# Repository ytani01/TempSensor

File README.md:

# 環境センサー類(温度、湿度など)

* [BME280](BME280/)
* [SHT-31](SHT-31/)

## beebottle python library

https://github.com/beebotte/bbt_python

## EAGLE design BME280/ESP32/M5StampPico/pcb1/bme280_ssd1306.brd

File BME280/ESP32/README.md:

# BME280(I2C) and ESP32

## !! IMPORTANT !!

FORCEDモードにしないと、温度がかなり高めにでる!

```c++
:
#include <Adafruit_BME280.h>

const uint8_t I2CADDR_BME280 = 0x76;

Adafruit_BME280 bme;

void setup() {

  bme.begin(I2CADDR_BME280);
  bme.setSampling(Adafruit_BME280::MODE_FORCED);  // !! IMPORTANT !!

}

void loop() {

  bme.takeForcedMeasurement();  // !! IMPORTANT !!

  float temp = bme.readTemperature();
  float humidity = bme.readHumidity();
  
}
```

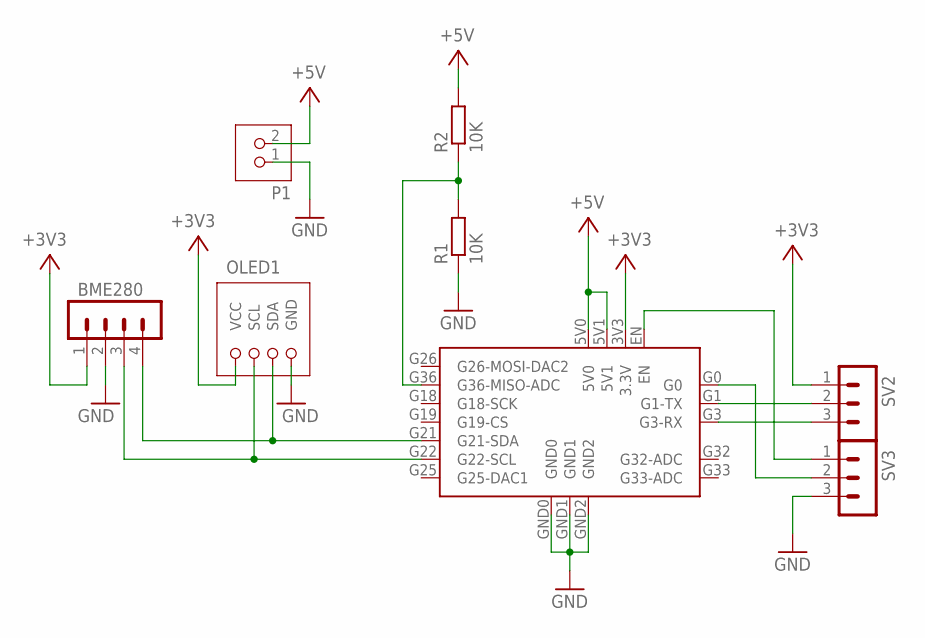
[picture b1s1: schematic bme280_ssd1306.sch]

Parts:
BME280: PINHEAD-MA04-1
M5PICO1: M5STAMP-PICO-SMD
OLED1: OLED-SSD1306-0.96; OLED-I2C-0.96
P1: JST-PH2
R1, R2: 10K; R3216
SV2, SV3: PINHEAD-MA03-1

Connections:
+3V3: BME280.1, M5PICO1.3V3 (3.3V), OLED1.VCC, SV2.1
+5V: M5PICO1.5V0, M5PICO1.5V1, P1.2, R2.2
GND: BME280.2, M5PICO1.GND0, M5PICO1.GND1, M5PICO1.GND2, OLED1.GND, P1.1, R1.1, SV3.3
unnamed: M5PICO1.G1 (G1-TX), SV2.2
unnamed: M5PICO1.G3 (G3-RX), SV2.3
unnamed: M5PICO1.EN, SV3.1
unnamed: M5PICO1.G0, SV3.2
unnamed: BME280.4, M5PICO1.G21 (G21-SDA), OLED1.SDA
unnamed: BME280.3, M5PICO1.G22 (G22-SCL), OLED1.SCL
unnamed: M5PICO1.G36 (G36-MISO-ADC), R1.2, R2.1

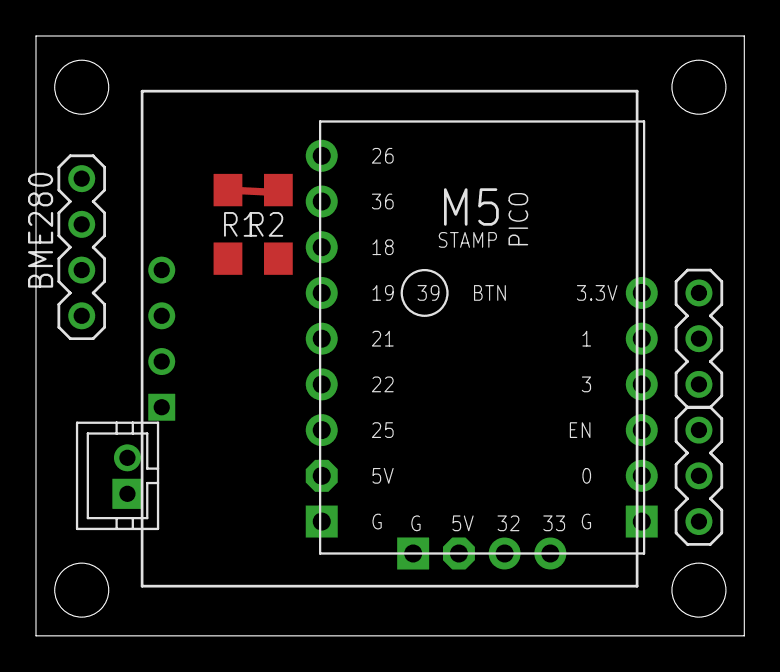
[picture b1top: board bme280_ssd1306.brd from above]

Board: 2 copper layers, 39.4 x 33.3 mm, 8 parts (0 on the bottom side), 10 nets.

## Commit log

2019-01-18 SHT-31
2019-01-18 README.md
2019-04-21 handle I2C Error
2019-11-12 subscriber
2020-06-19 update_t
2021-08-26 UPD: Bme280publisher.py
2021-08-26 UPD: .gitignore
2021-10-07 ADD: BME280/RaspberryPi/, BME280/ESP32/
2021-10-07 ADD: BME280/ESP32/tests/
2022-01-16 ADD: BME280/ESP32/M5StampPico/oled1/
2022-01-16 UPD: M5StampPico/ssd1306-1/
2022-01-16 ADD: pcb1/
2022-01-16 UPD: BME280/RaspberryPi/
2022-01-17 UPD: M5StampPico/ssd1306-2/
2022-01-18 ADD: M5StampPico/temp-oled-wifi-1/
2022-01-18 START: M5StampPico/temp-oled-wifi-1 v0.2
2022-01-18 UPD: M5StampPico/temp-oled-wifi-1
2023-06-30 UPD: BME280/RaspberryPi/Bme280publisher.py: mqtt.ytani.net .. T.B.D.
2023-07-18 UPD: BME280/RaspberryPi/Bme280publisher.py: Decimal
